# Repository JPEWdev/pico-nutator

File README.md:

# pico-nutator

This repository contains the source code and KiCad Schematic and PCB for a Pico
Pi powered scientific rocker (e.g. a nutator). The machine is designed to mix
small quantities of liquid (i.e. test tubes) by gently rocking them back and
forth or around in circles.

This is for a homemade rocker that I built. While the one I built is just a
rocker and not actually a [nutator](https://en.wikipedia.org/wiki/Nutation),
the software and hardware design could be utilized with different mechanical
designs.

## Basic hardware design

The PCB routes power from a 12V power brick, through a power switch, then out
to a 3 pin connector. This connector goes to a commonly available L298N dual
H-bridge board. This stepper motor driver provide back 5V power, courtesy of an
on board linear regulator.

A Raspberry Pi Pico is the brains of the system. It has 4 motor outputs driven
via PWM to L298N motor controller board to drive the 2 poles of a stepper motor
using the dual H-bridge. These outputs are driven via PWM to ensure that the
motor does not exceed its rated current limit. In addition there is a motor
enable output pin which goes to the L298N to completely disable the H-bridge,
allowing the motor to spin freely. This is important because the stepper motor
will draw current when it is locked in place, wasting power. If the rocker is
not running and has no inputs for 60 seconds, it will go into "sleep mode" and
disable the H-bridge to save energy.

For input, there are 3 buttons; a Start/Stop button to start and stop the
motor, and an up and down button to increase or decrease the target RPM of the
motor. The target RPM can be changed while the motor is stopped, or running.
The software will also apply acceleration to the motor RPM, so that it smoothly
ramps up or down to the target RPM when starting or when the RPM has changed.
When changing speed, the display will show the percentage of the target speed
the motor is currently running at.

For display, the Pico Pi is connected to a Newhaven K3Z family 2x16 LCD.

Finally, a fan output is enabled when the motor is enabled to cool the L298N,
as it can get hot while running. The fan turns off in sleep mode.

The Schematic and PCB were designed in [KiCad](https://www.kicad.org/)

## Software

The software is written in C using the [Pico Pi SDK](https://www.raspberrypi.com/documentation/pico-sdk/).
An initial prototype was written in Python using
[CircuitPython](https://circuitpython.org/), however it had to be re-written in
C since the overhead and jitter in the Python code made it unable to get
precise timing on motor output pins, and thus it did not run smoothly,
especially at high RPM (e.g. above 30)

## Compiling and Installing

To build the software yourself first ensure that you have a suitable cross
compiler installed to compile for the Pico Pi (I used GCC, but presume Clang
would work also). First, the Pico Pi SDK must be fetched as a submodule using:

```shell
git submodule update --init --recursive
```

Next, make a build directory, configure it using `cmake`, and build using
`ninja` (using `ninja` is recommended, as it will result in a faster build of
the SDK):

```shell
mkdir build
cd build
cmake .. -GNinja
ninja
```

To load the software onto the Pico Pi, ensure it is not powered, then hold down
the `BOOTSEL` button while plugging it into the USB port of your computer. The
Pico Pi will show up as a removal USB drive. Copy the `nutator.bin` file to
this USB drive, and the Pico Pi will automatically reboot and start executing
the program.

## Final Assembly

Here is a picture of the final assembled rocker I built:

And here is a close up of the electronics with the control board and H-bridge
labeled:

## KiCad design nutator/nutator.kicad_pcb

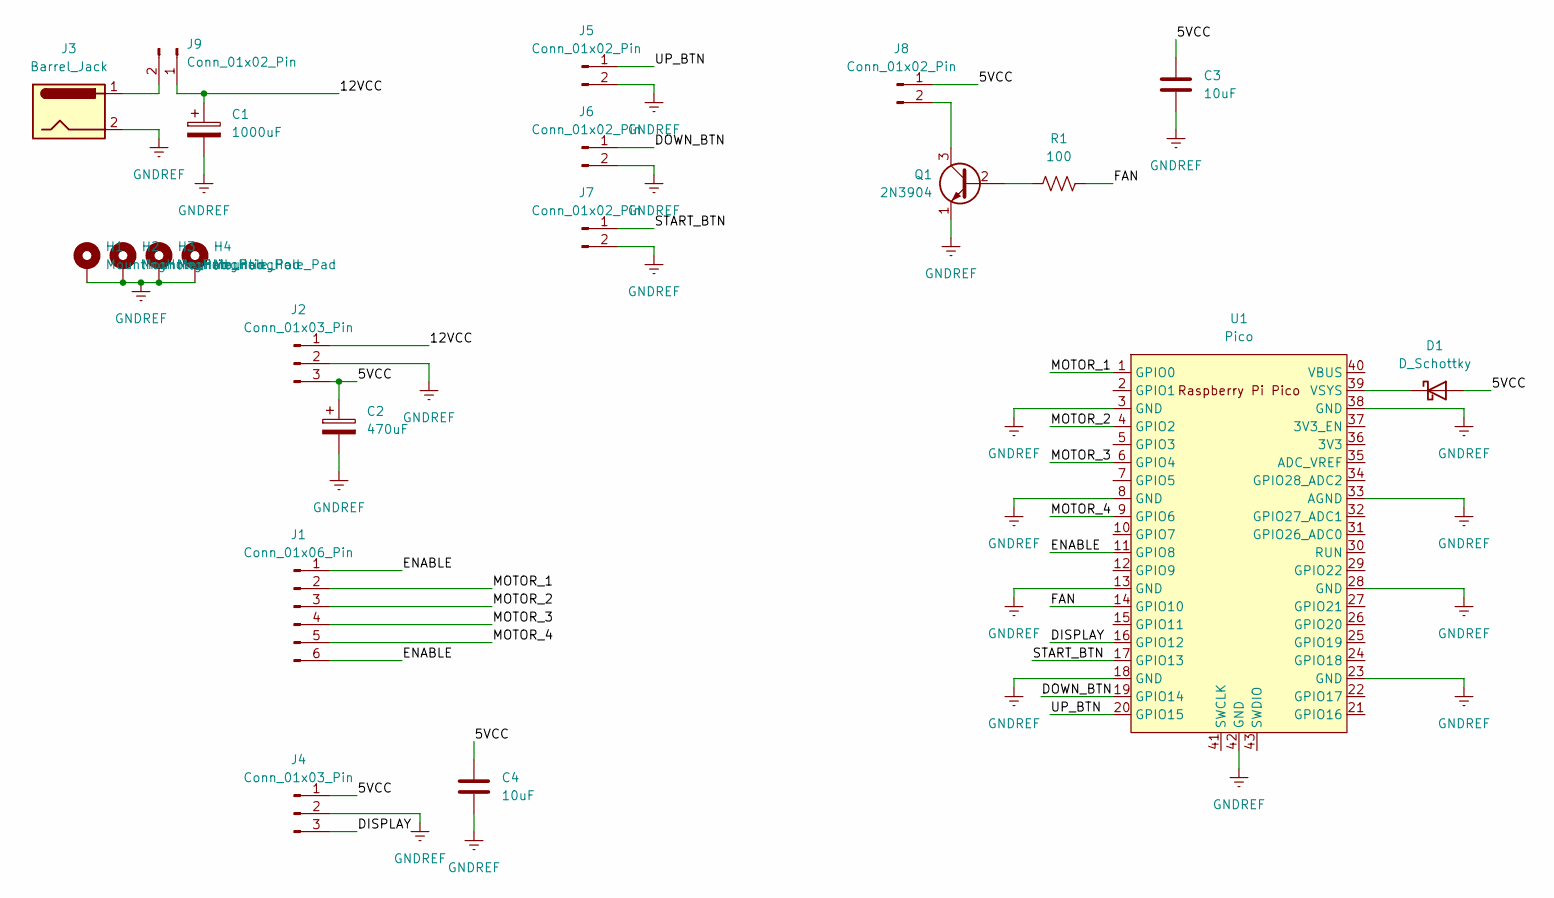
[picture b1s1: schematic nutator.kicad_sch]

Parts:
C1: 1000uF; CP_Radial_D8.0mm_P3.50mm
C2: 470uF; CP_Radial_D8.0mm_P3.50mm
C3, C4: 10uF; C_0603_1608Metric_Pad1.08x0.95mm_HandSolder
D1: D_Schottky; D_SOD-123F
H1, H2, H3, H4: MountingHole_Pad; MountingHole_3.2mm_M3_ISO7380_Pad
J1: Conn_01x06_Pin; PinHeader_1x06_P2.54mm_Vertical
J2, J4: Conn_01x03_Pin; PinHeader_1x03_P2.54mm_Vertical
J3: Barrel_Jack; BarrelJack_CUI_PJ-036AH-SMT_Horizontal
J5, J6, J7, J8, J9: Conn_01x02_Pin; PinHeader_1x02_P2.54mm_Vertical
Q1: 2N3904; TO-92_Inline
R1: 100; R_0603_1608Metric_Pad0.98x0.95mm_HandSolder
U1: Pico; RPi_Pico_SMD_TH

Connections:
/5VCC: C2.1, C3.1, C4.1, D1.2 (A), J2.3, J4.1, J8.1
/12VCC: C1.1, J2.1, J9.1
/DISPLAY: J4.3, U1.16 (GPIO12)
/DOWN_BTN: J6.1, U1.19 (GPIO14)
/ENABLE: J1.1, J1.6, U1.11 (GPIO8)
/FAN: R1.2, U1.14 (GPIO10)
/MOTOR_1: J1.2, U1.1 (GPIO0)
/MOTOR_2: J1.3, U1.4 (GPIO2)
/MOTOR_3: J1.4, U1.6 (GPIO4)
/MOTOR_4: J1.5, U1.9 (GPIO6)
/START_BTN: J7.1, U1.17 (GPIO13)
/UP_BTN: J5.1, U1.20 (GPIO15)
GNDREF: C1.2, C2.2, C3.2, C4.2, H1.1, H2.1, H3.1, H4.1, J2.2, J3.2, J4.2, J5.2, J6.2, J7.2, Q1.1 (E), U1.3 (GND), U1.8 (GND), U1.13 (GND), U1.18 (GND), U1.23 (GND), U1.28 (GND), U1.33 (AGND), U1.38 (GND), U1.42 (GND)
unnamed: D1.1 (K), U1.39 (VSYS)
unnamed: J8.2, Q1.3 (C)
unnamed: J3.1, J9.2
unnamed: Q1.2 (B), R1.1

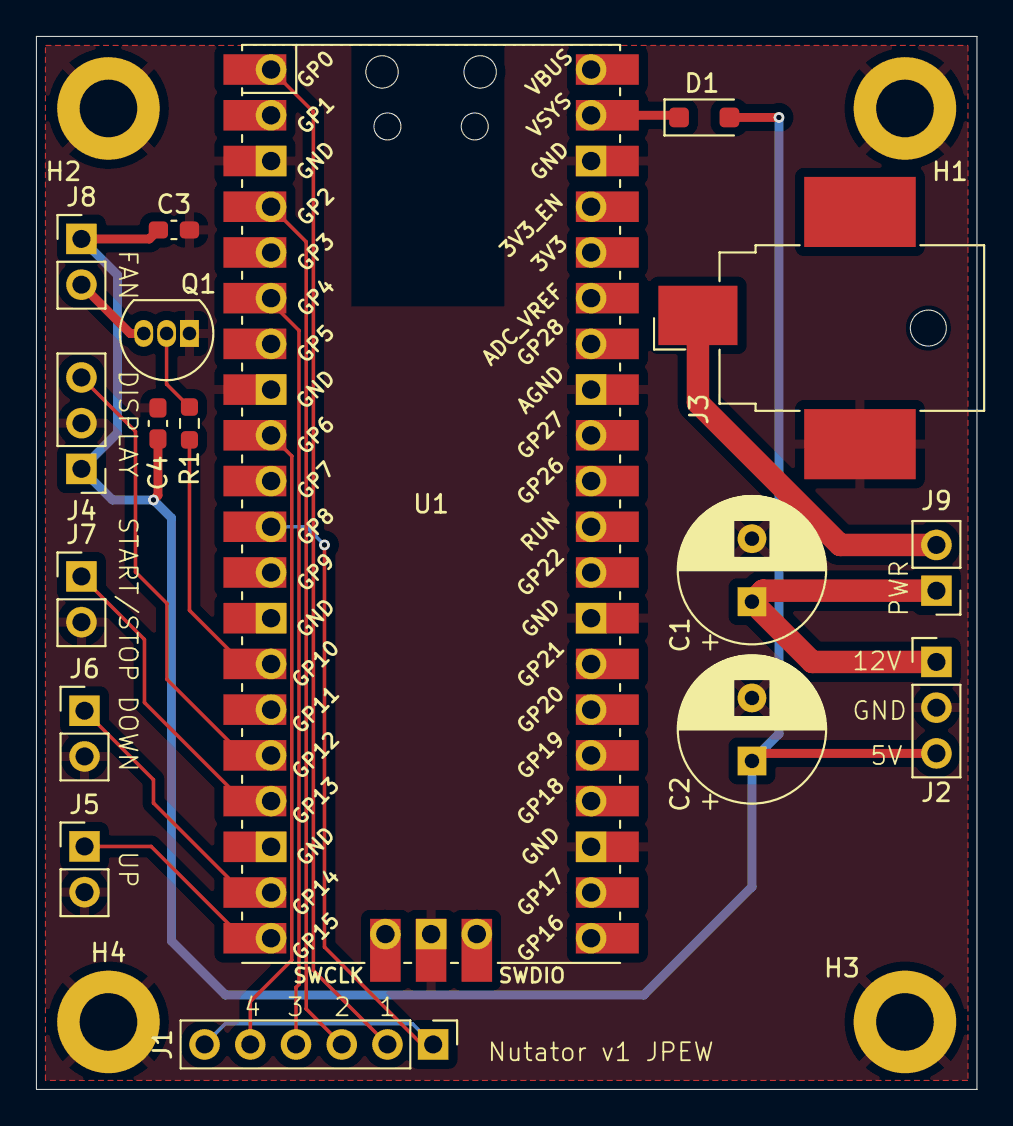
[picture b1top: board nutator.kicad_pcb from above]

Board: 2 copper layers, 52.2 x 58.5 mm, 21 parts (0 on the bottom side), 17 nets.

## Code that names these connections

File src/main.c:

/*
 * SPDX-License-Identifier: MIT
 *
 * Copyright (c) 2024 Joshua Watt
 */
#include <inttypes.h>
#include <stdio.h>

#include "button.h"
#include "hardware/pwm.h"
#include "nhd-k3z.h"
#include "persist.h"
#include "pico/stdlib.h"
#include "stepper-motor.h"

#define VERSION "1.0"

#define MAX_RPM (60)
#define RPM_STEP (5)
#define STEPS_PER_REV (200)
#define SLEEP_TIMEOUT_US (60 * 1000000)

/*
 * Frequency is high so that the stepper motor is (more or less) not audible
 * when holding
 */
#define MOTOR_FREQUENCY (15000)

/*
 * Power supply is 12V, the motor is rated for 1.5 Amps max, with a resistance
 * of 2.3 Ohms. In an ideal world, this would normally be a 28% duty cycle,
 * however the frequency of our PWM is quite a bit above the cutoff frequency
 * of the motor (4 mH inductance, cutoff is 91 Hz), so lot of attenuation is
 * happening, and there is a pretty non-linear response to the duty cycle
 * because of this.
 *
 * As such, this was determined empirically, mostly by checking if the stepper
 * motor driver was too hot to touch
 */
#define MOTOR_DUTY_CYCLE (40)

#define MOTOR_ACCEL (60)

#define LED_PIN (25)

#define ARRAY_COUNT(arr) (sizeof(arr) / sizeof(arr[0]))

/*
 * Motor uses even pins so that each can has its own independent PWM. This is
 * in case I want to do micro-stepping some day
 */
static const unsigned int motor_pins[] = {0, 4, 2, 6};

/*
 * Motor enable pin is also even in case we want to independently PWM it
 */
#define MOTOR_ENABLE_PIN (8)

/*
 * Fan pin is also even in case we want to independently PWM it
 */
#define FAN_PIN (10)

#define DISPLAY_PIN (12)
#define DISPLAY_UART (uart0)

#define START_STOP_BTN_PIN (13)
#define DOWN_BTN_PIN (14)
#define UP_BTN_PIN (15)

static struct button* make_button(int pin) {
    struct button* b = button_create(pin, true, 35);
    gpio_pull_up(pin);
    button_set_repeat(b, 1000, 500);
    return b;
}

bool run = false;
uint64_t run_time_start = 0;
bool sleeping = false;
struct nhdk3z* display;
struct stepper* motor;

struct persist persist;

struct hms {
    unsigned int hours;
    unsigned int minutes;
    unsigned int seconds;
};

static struct hms us_to_hms(uint64_t us) {
    struct hms result;

    result.hours = us / (1000000ull * 60 * 60);
    result.minutes = (us / (1000000ull * 60)) % 60;
    result.seconds = (us / 1000000ull) % 60;

    return result;
}

static void set_target_rpm(unsigned int new_rpm) {
    new_rpm = MAX(new_rpm, RPM_STEP);
    new_rpm = MIN(new_rpm, MAX_RPM);

    persist.target_rpm = new_rpm;
    if (run) {
        stepper_set_rpm(motor, persist.target_rpm);
    }

    printf("Target RPM is now %" PRIu32 "\n", persist.target_rpm);
}

static void update_display() {
    if (sleeping) {
        return;
    }

    nhdk3z_clear(display);
    nhdk3z_home(display);
    if (run) {
        struct hms hms = us_to_hms(time_us_64() - run_time_start);

        nhdk3z_printf(display, "Running %u:%02u:%02u", hms.hours, hms.minutes,
                      hms.seconds);
    } else {
        nhdk3z_write(display, "Stopped");
    }
    nhdk3z_set_cursor(display, 0x40);
    nhdk3z_printf(display, "RPM %d", persist.target_rpm);
    if (run) {
        unsigned int actual_rpm = stepper_get_actual_rpm(motor);
        if (actual_rpm && actual_rpm != persist.target_rpm) {
            nhdk3z_printf(display, " (%d%%)",
                          100 * actual_rpm / persist.target_rpm);
        }
    }
}

static void set_sleep(bool sleep) {
    if (sleeping == sleep) {
        return;
    }

    sleeping = sleep;

    stepper_enable(motor, !sleeping);
    if (sleeping) {
        nhdk3z_set_brightness(display, 1);
        gpio_put(FAN_PIN, 0);
    } else {
        nhdk3z_set_brightness(display, 8);
        stepper_hold(motor);
        gpio_put(FAN_PIN, 1);
        update_display();
    }
}

static uint32_t pwm_set_freq_duty(unsigned int slice_num, unsigned int chan,
                                  uint32_t frequency, int duty) {
    uint32_t clock = 125000000;
    uint32_t divider16 =
        clock / frequency / 4096 + (clock % (frequency * 4096) != 0);
    if (divider16 / 16 == 0) {
        divider16 = 16;
    }
    uint32_t wrap = clock * 16 / divider16 / frequency - 1;
    pwm_set_clkdiv_int_frac(slice_num, divider16 / 16, divider16 & 0xF);
    pwm_set_wrap(slice_num, wrap);
    pwm_set_chan_level(slice_num, chan, wrap * duty / 100);
    return wrap;
}

int main() {
    stdio_init_all();
    gpio_init(LED_PIN);
    gpio_set_dir(LED_PIN, GPIO_OUT);
    gpio_put(LED_PIN, 1);
    printf("Booting...");
    /* Wait for display to power up */
    sleep_ms(1000);
    read_persist(&persist);

    /* Buttons */
    struct button* up_button = make_button(UP_BTN_PIN);
    struct button* down_button = make_button(DOWN_BTN_PIN);
    struct button* start_stop_button = make_button(START_STOP_BTN_PIN);

    /* Fan */
    gpio_init(FAN_PIN);
    gpio_set_dir(FAN_PIN, GPIO_OUT);
    gpio_put(FAN_PIN, 0);

    /* Motor */
    /*
     * The motor is driven in half-step mode. This results in uneven torque and
     * lower average torque than dual phase stepping, since each alternating
     * step uses either 1 or 2 phases of the motor. However, the motor runs
     * much smoother since it effectively doubles the number of steps
     */
    motor = stepper_create(STEPS_PER_REV, MAX_RPM, STEPPER_MODE_HALF_STEP,
                           MOTOR_ENABLE_PIN);

    uint32_t pwm_mask = 0;
    for (int i = 0; i < ARRAY_COUNT(motor_pins); i++) {
        unsigned int slice_num = pwm_gpio_to_slice_num(motor_pins[i]);
        unsigned int chan = pwm_gpio_to_channel(motor_pins[i]);
        pwm_set_freq_duty(slice_num, chan, MOTOR_FREQUENCY, MOTOR_DUTY_CYCLE);
        stepper_add_pin(motor, motor_pins[i], true);
        pwm_mask |= 1 << slice_num;
    }
    pwm_set_mask_enabled(pwm_mask);

    /* Display */
    display = nhdk3z_create(DISPLAY_UART);
    gpio_set_function(DISPLAY_PIN, GPIO_FUNC_UART);
    nhdk3z_set_baud(display, NHDK3Z_BAUD_57600);

    nhdk3z_set_display_on(display, true);
    nhdk3z_set_contrast(display, 50);
    nhdk3z_set_brightness(display, 8);
    nhdk3z_set_cursor_blink(display, false);
    nhdk3z_set_cursor_underline(display, false);
    nhdk3z_clear(display);
    nhdk3z_home(display);
    nhdk3z_printf(display, "Version %s", VERSION);
    sleep_ms(2000);

    stepper_set_accel(motor, MOTOR_ACCEL, RPM_STEP);
    stepper_enable(motor, true);
    stepper_hold(motor);
    update_display();
    gpio_put(FAN_PIN, 1);

    uint64_t sleep_start = time_us_64();
    int run_time_sec = 0;

    while (true) {
        uint64_t now = time_us_64();
        bool redraw = false;

        if (!run && !sleeping && now >= sleep_start + SLEEP_TIMEOUT_US) {
            set_sleep(true);
        }

        /*
         * Redraw if running and the seconds have changed
         */
        if (run) {
            struct hms hms = us_to_hms(now - run_time_start);
            if (hms.seconds != run_time_sec) {
                redraw = true;
                run_time_sec = hms.seconds;
            }
        }

        gpio_put(LED_PIN, stepper_update(motor) ? 1 : 0);
        button_update(up_button);
        button_update(down_button);
        button_update(start_stop_button);

        if (sleeping) {
            if (button_up(up_button) || button_up(down_button) ||
                button_up(start_stop_button)) {
                set_sleep(false);
                sleep_start = now;
            }
        } else {
            if (button_repeat(up_button)) {
                set_target_rpm(persist.target_rpm + RPM_STEP);
                sleep_start = now;
                redraw = true;
            }

            if (button_repeat(down_button)) {
                set_target_rpm(persist.target_rpm - RPM_STEP);
                sleep_start = now;
                redraw = true;
            }

            if (!run && button_is_pressed(start_stop_button) &&
                button_current_duration_us(start_stop_button) >= 4000000) {
                nhdk3z_clear(display);
                nhdk3z_home(display);
                nhdk3z_write(display, "Sleeping...");
                sleep_ms(1000);
                set_sleep(true);
                while (!button_up(start_stop_button)) {
                    button_update(start_stop_button);
                }
            } else if (button_up(start_stop_button)) {
                run = !run;
                write_persist(&persist);
                if (run) {
                    stepper_set_rpm(motor, persist.target_rpm);
                    run_time_start = now;
                    run_time_sec = 0;
                } else {
                    stepper_set_rpm(motor, 0);
                }
                sleep_start = now;
                redraw = true;
            }
        }

        if (redraw) {
            update_display();
        }
    }

    return 0;
}

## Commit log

2024-08-25 Initial Implementation
2024-08-25 README.md: Add images
    Adds images of the final assembled rocker to the README.md
2024-08-25 Improve comments
    Improves some comments for clarity
